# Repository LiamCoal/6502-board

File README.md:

# 6502-board
*Experimental 6502 computer.*

## ...why?
Just because I wanted to make something that was not a microcontroller stuck on a board with some capacitors and resistors...

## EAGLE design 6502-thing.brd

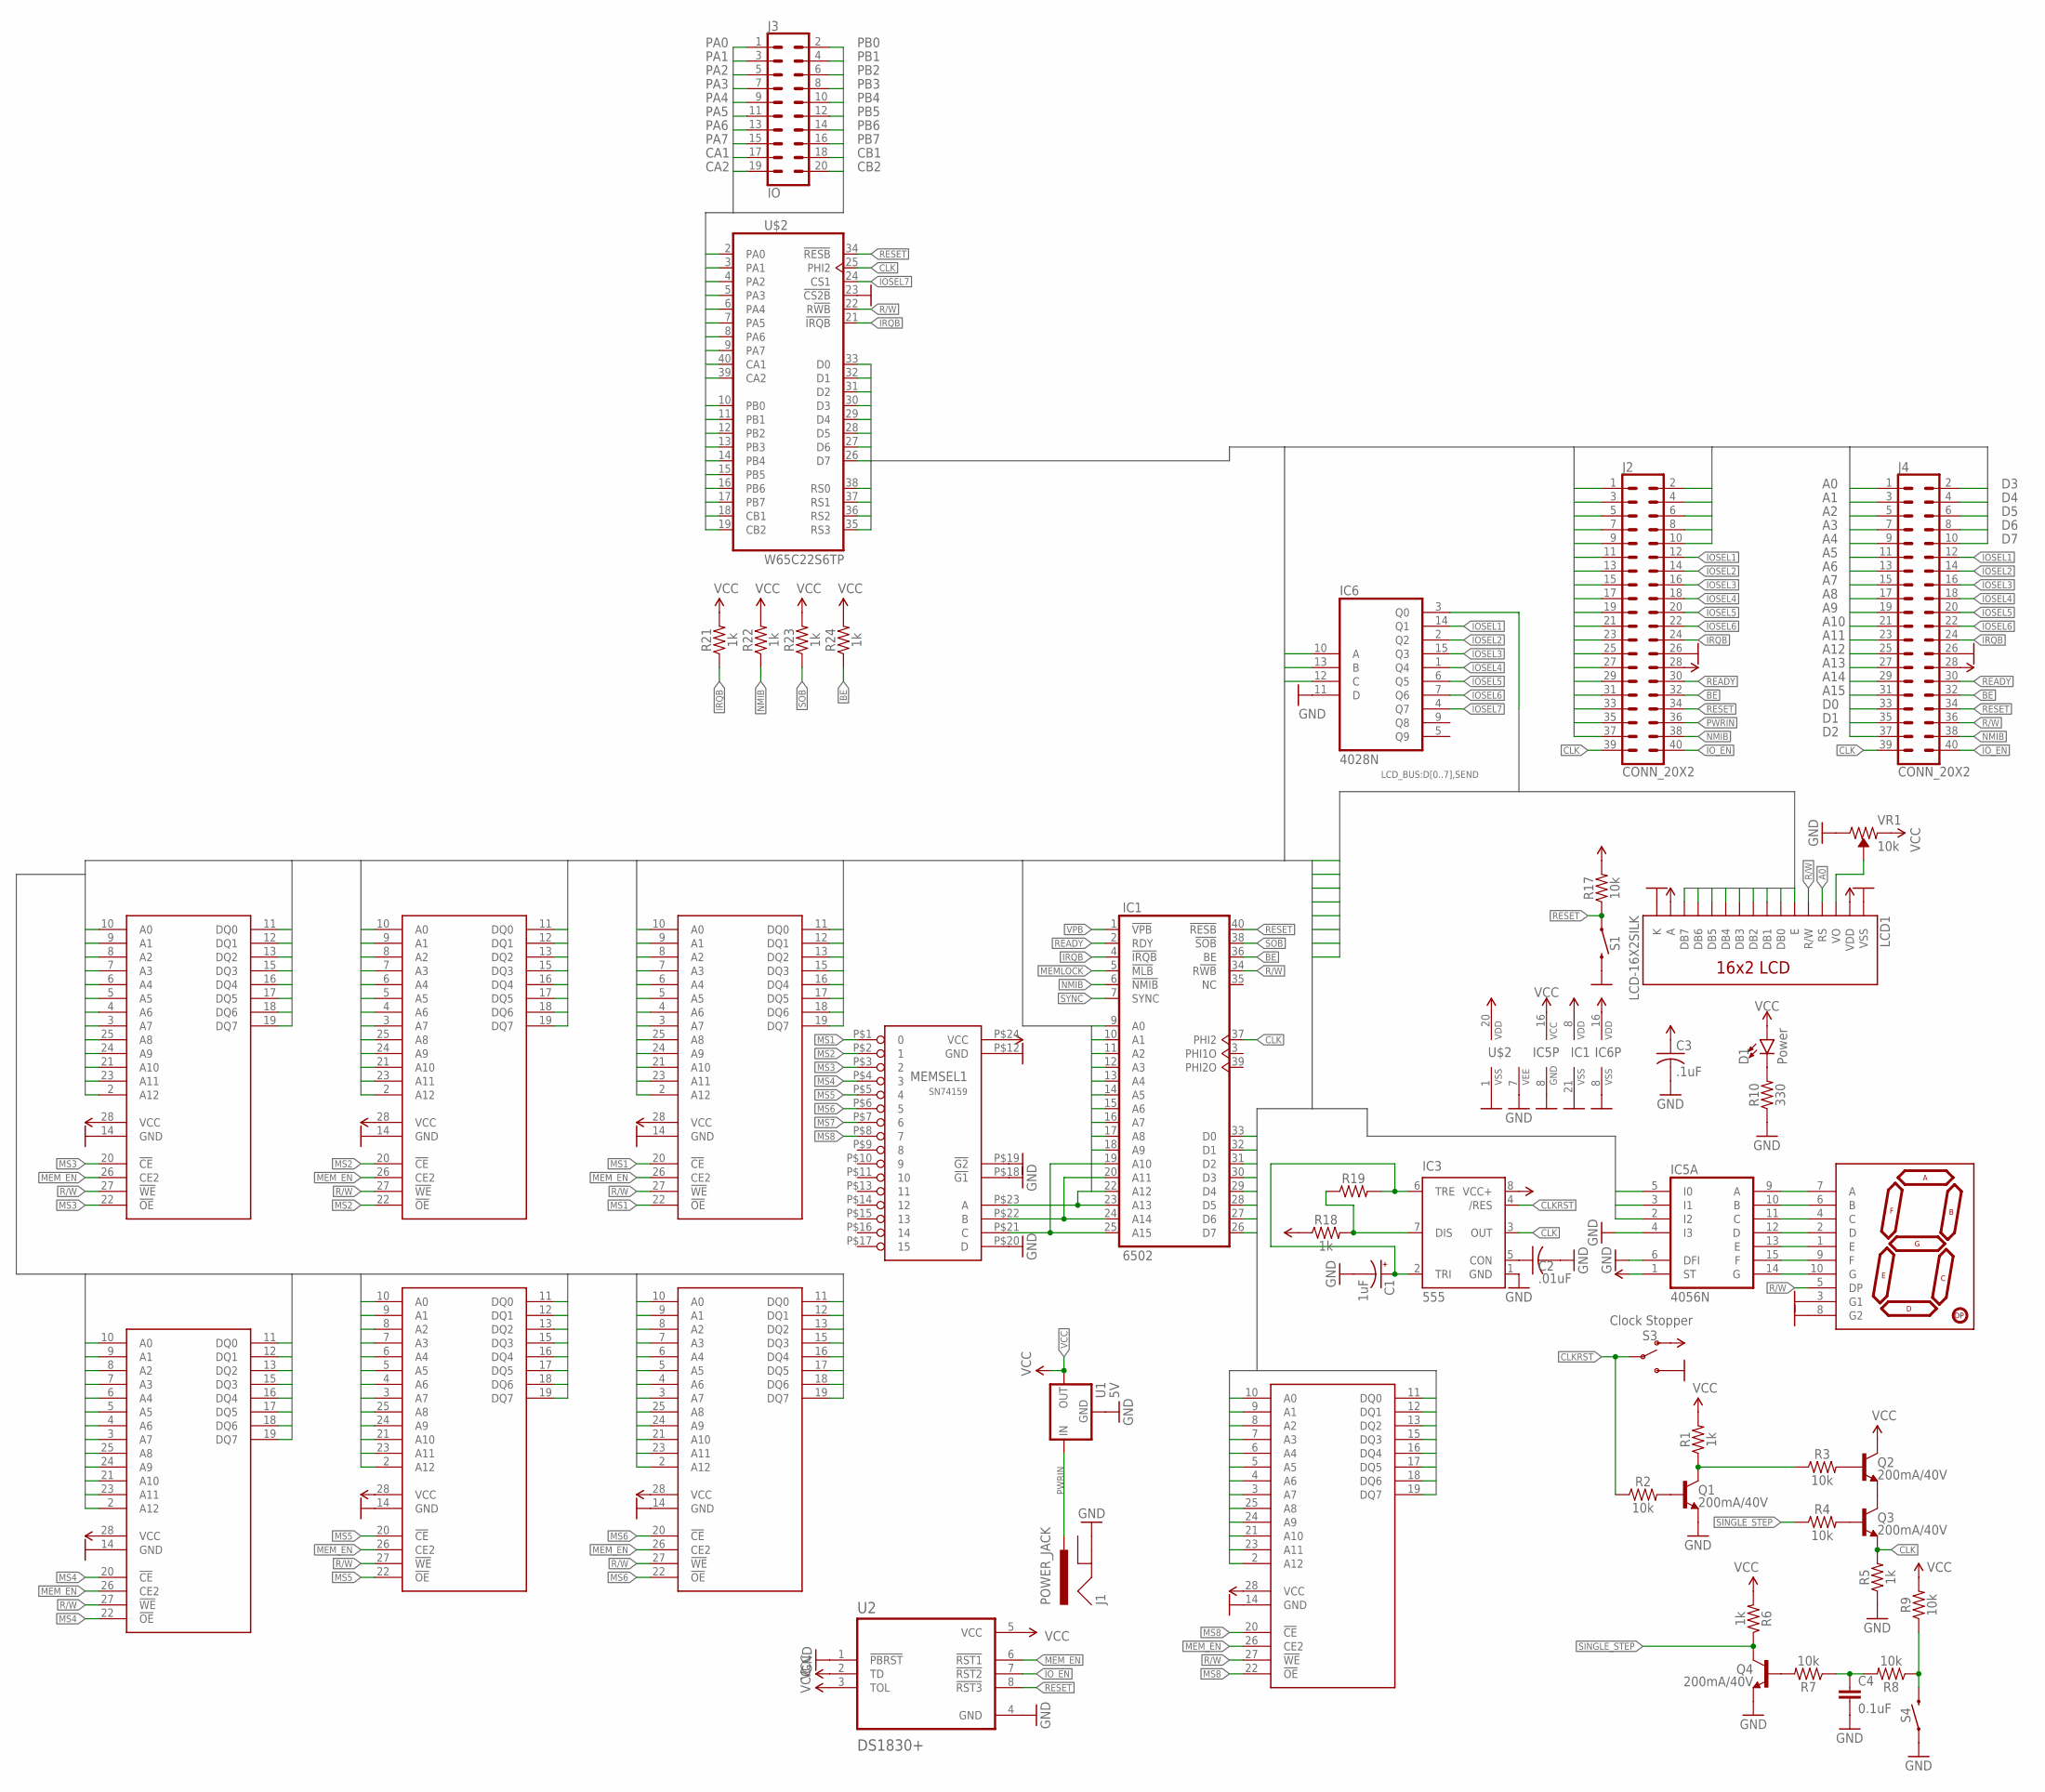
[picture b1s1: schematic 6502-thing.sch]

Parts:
C1: 1uF; E3,5-8
C2: .01uF; C025-024X044
C3: .1uF; C025-024X044
C4: 0.1uF; CAP-PTH-SMALL-KIT
D1: Power; LED_5MM
EEPROM1: AS6C6264DIP28; 0.6"_DIP28
IC1: 6502; DIL40
IC3: 555; DIP08
IC5: 4056N; DIL16
IC6: 4028N; DIL16
J1: POWER_JACK; POWER_JACK_PTH
J2, J4: CONN_20X2; 2X20
J3: IO; 2X10
LCD1: LCD-16X2SILK; LCD-16X2
MEMORY1, MEMORY2, MEMORY3, MEMORY4, MEMORY5, MEMORY6: AS6C6264DIP28; 0.6"_DIP28
MEMSEL1: SN74159; 0.6"_DIP24
Q1, Q2, Q3, Q4: 200mA/40V; TO-92
R1, R5, R6, R18, R19, R21, R22, R23, R24: 1k; AXIAL-0.3
R2, R3, R4, R7, R8, R9, R17: 10k; AXIAL-0.3
R10: 330; AXIAL-0.3
S1, S4: MOMENTARY-SWITCH-SPST-PTH-6.0MM; TACTILE_SWITCH_PTH_6.0MM
S3: Clock Stopper; SWITCH_SPDT_PTH_11.6X4.0MM
U1: 5V; TO-220-ALT
U2: DS1830+; DIP794W47P254L991H457Q8
U$1: YSD-160AB3C-8; 7-SEGMENT-1"PTH
U$2: W65C22S6TP; DIL40
VR1: 10k; TRIMPOT-PTH-3386U

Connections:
A0: EEPROM1.10 (A0), IC1.9 (A0), J2.1, J4.1, LCD1.4 (RS), MEMORY1.10 (A0), MEMORY2.10 (A0), MEMORY3.10 (A0), MEMORY4.10 (A0), MEMORY5.10 (A0), MEMORY6.10 (A0), U$2.38 (RS0)
A1: EEPROM1.9 (A1), IC1.10 (A1), J2.3, J4.3, MEMORY1.9 (A1), MEMORY2.9 (A1), MEMORY3.9 (A1), MEMORY4.9 (A1), MEMORY5.9 (A1), MEMORY6.9 (A1), U$2.37 (RS1)
A2: EEPROM1.8 (A2), IC1.11 (A2), J2.5, J4.5, MEMORY1.8 (A2), MEMORY2.8 (A2), MEMORY3.8 (A2), MEMORY4.8 (A2), MEMORY5.8 (A2), MEMORY6.8 (A2), U$2.36 (RS2)
A3: EEPROM1.7 (A3), IC1.12 (A3), J2.7, J4.7, MEMORY1.7 (A3), MEMORY2.7 (A3), MEMORY3.7 (A3), MEMORY4.7 (A3), MEMORY5.7 (A3), MEMORY6.7 (A3), U$2.35 (RS3)
A4: EEPROM1.6 (A4), IC1.13 (A4), J2.9, J4.9, MEMORY1.6 (A4), MEMORY2.6 (A4), MEMORY3.6 (A4), MEMORY4.6 (A4), MEMORY5.6 (A4), MEMORY6.6 (A4)
A5: EEPROM1.5 (A5), IC1.14 (A5), J2.11, J4.11, MEMORY1.5 (A5), MEMORY2.5 (A5), MEMORY3.5 (A5), MEMORY4.5 (A5), MEMORY5.5 (A5), MEMORY6.5 (A5)
A6: EEPROM1.4 (A6), IC1.15 (A6), J2.13, J4.13, MEMORY1.4 (A6), MEMORY2.4 (A6), MEMORY3.4 (A6), MEMORY4.4 (A6), MEMORY5.4 (A6), MEMORY6.4 (A6)
A7: EEPROM1.3 (A7), IC1.16 (A7), J2.15, J4.15, MEMORY1.3 (A7), MEMORY2.3 (A7), MEMORY3.3 (A7), MEMORY4.3 (A7), MEMORY5.3 (A7), MEMORY6.3 (A7)
A8: EEPROM1.25 (A8), IC1.17 (A8), J2.17, J4.17, MEMORY1.25 (A8), MEMORY2.25 (A8), MEMORY3.25 (A8), MEMORY4.25 (A8), MEMORY5.25 (A8), MEMORY6.25 (A8)
A9: EEPROM1.24 (A9), IC1.18 (A9), J2.19, J4.19, MEMORY1.24 (A9), MEMORY2.24 (A9), MEMORY3.24 (A9), MEMORY4.24 (A9), MEMORY5.24 (A9), MEMORY6.24 (A9)
A10: EEPROM1.21 (A10), IC1.19 (A10), IC6.10 (A), J2.21, J4.21, MEMORY1.21 (A10), MEMORY2.21 (A10), MEMORY3.21 (A10), MEMORY4.21 (A10), MEMORY5.21 (A10), MEMORY6.21 (A10)
A11: EEPROM1.23 (A11), IC1.20 (A11), IC6.13 (B), J2.23, J4.23, MEMORY1.23 (A11), MEMORY2.23 (A11), MEMORY3.23 (A11), MEMORY4.23 (A11), MEMORY5.23 (A11), MEMORY6.23 (A11)
A12: EEPROM1.2 (A12), IC1.22 (A12), IC6.12 (C), J2.25, J4.25, MEMORY1.2 (A12), MEMORY2.2 (A12), MEMORY3.2 (A12), MEMORY4.2 (A12), MEMORY5.2 (A12), MEMORY6.2 (A12)
A13: IC1.23 (A13), IC5.5 (I0), J2.27, J4.27, MEMSEL1.P$23 (A)
A14: IC1.24 (A14), IC5.3 (I1), J2.29, J4.29, MEMSEL1.P$22 (B)
A15: IC1.25 (A15), IC5.2 (I2), J2.31, J4.31, MEMSEL1.P$21 (C)
BE: IC1.36 (BE), J2.32, J4.32, R24.P$1 (1)
CA1: J3.17, U$2.40 (CA1)
CA2: J3.19, U$2.39 (CA2)
CB1: J3.18, U$2.18 (CB1)
CB2: J3.20, U$2.19 (CB2)
CLK: IC1.37 (PHI2), IC3.3 (OUT), J2.39, J4.39, Q3.1 (E), R5.P$2 (2), U$2.25 (PHI2)
CLKRST: IC3.4 (/RES), R2.P$1 (1), S3.2
D0: EEPROM1.11 (DQ0), IC1.33 (D0), J2.33, J4.33, LCD1.7 (DB0), MEMORY1.11 (DQ0), MEMORY2.11 (DQ0), MEMORY3.11 (DQ0), MEMORY4.11 (DQ0), MEMORY5.11 (DQ0), MEMORY6.11 (DQ0), U$2.33 (D0)
D1: EEPROM1.12 (DQ1), IC1.32 (D1), J2.35, J4.35, LCD1.8 (DB1), MEMORY1.12 (DQ1), MEMORY2.12 (DQ1), MEMORY3.12 (DQ1), MEMORY4.12 (DQ1), MEMORY5.12 (DQ1), MEMORY6.12 (DQ1), U$2.32 (D1)
D2: EEPROM1.13 (DQ2), IC1.31 (D2), J2.37, J4.37, LCD1.9 (DB2), MEMORY1.13 (DQ2), MEMORY2.13 (DQ2), MEMORY3.13 (DQ2), MEMORY4.13 (DQ2), MEMORY5.13 (DQ2), MEMORY6.13 (DQ2), U$2.31 (D2)
D3: EEPROM1.15 (DQ3), IC1.30 (D3), J2.2, J4.2, LCD1.10 (DB3), MEMORY1.15 (DQ3), MEMORY2.15 (DQ3), MEMORY3.15 (DQ3), MEMORY4.15 (DQ3), MEMORY5.15 (DQ3), MEMORY6.15 (DQ3), U$2.30 (D3)
D4: EEPROM1.16 (DQ4), IC1.29 (D4), J2.4, J4.4, LCD1.11 (DB4), MEMORY1.16 (DQ4), MEMORY2.16 (DQ4), MEMORY3.16 (DQ4), MEMORY4.16 (DQ4), MEMORY5.16 (DQ4), MEMORY6.16 (DQ4), U$2.29 (D4)
D5: EEPROM1.17 (DQ5), IC1.28 (D5), J2.6, J4.6, LCD1.12 (DB5), MEMORY1.17 (DQ5), MEMORY2.17 (DQ5), MEMORY3.17 (DQ5), MEMORY4.17 (DQ5), MEMORY5.17 (DQ5), MEMORY6.17 (DQ5), U$2.28 (D5)
D6: EEPROM1.18 (DQ6), IC1.27 (D6), J2.8, J4.8, LCD1.13 (DB6), MEMORY1.18 (DQ6), MEMORY2.18 (DQ6), MEMORY3.18 (DQ6), MEMORY4.18 (DQ6), MEMORY5.18 (DQ6), MEMORY6.18 (DQ6), U$2.27 (D6)
D7: EEPROM1.19 (DQ7), IC1.26 (D7), J2.10, J4.10, LCD1.14 (DB7), MEMORY1.19 (DQ7), MEMORY2.19 (DQ7), MEMORY3.19 (DQ7), MEMORY4.19 (DQ7), MEMORY5.19 (DQ7), MEMORY6.19 (DQ7), U$2.26 (D7)
GND: C1.-, C2.2, C3.2, C4.2, EEPROM1.14 (GND), IC1.21 (VSS), IC3.1 (GND), IC5.4 (I3), IC5.6 (DFI), IC5.7 (VEE), IC5.8 (GND), IC6.8 (VSS), IC6.11 (D), J1.GND, J2.26, J4.26, LCD1.1 (VSS), LCD1.16 (K), MEMORY1.14 (GND), MEMORY2.14 (GND), MEMORY3.14 (GND), MEMORY4.14 (GND), MEMORY5.14 (GND), MEMORY6.14 (GND), MEMSEL1.P$12 (GND), MEMSEL1.P$18 (!G1!), MEMSEL1.P$19 (!G2!), MEMSEL1.P$20 (D), Q1.1 (E), Q4.1 (E), R5.P$1 (1), R10.P$1 (1), S1.3 (2), S3.3 (S), S4.1, U1.GND, U2.1 (!PBRST), U2.4 (GND), U$1.3 (G1), U$1.8 (G2), U$2.1 (VSS), U$2.23 (!CS2B), VR1.3 (CW)
IOSEL1: IC6.14 (Q1), J2.12, J4.12
IOSEL2: IC6.2 (Q2), J2.14, J4.14
IOSEL3: IC6.15 (Q3), J2.16, J4.16
IOSEL4: IC6.1 (Q4), J2.18, J4.18
IOSEL5: IC6.6 (Q5), J2.20, J4.20
IOSEL6: IC6.7 (Q6), J2.22, J4.22
IOSEL7: IC6.4 (Q7), U$2.24 (CS1)
IO_EN: J2.40, J4.40, U2.7 (!RST2)
IRQB: IC1.4 (!IRQB), J2.24, J4.24, R21.P$1 (1), U$2.21 (!IRQB)
MEMLOCK: IC1.5 (!MLB)
MEM_EN: EEPROM1.26 (CE2), MEMORY1.26 (CE2), MEMORY2.26 (CE2), MEMORY3.26 (CE2), MEMORY4.26 (CE2), MEMORY5.26 (CE2), MEMORY6.26 (CE2), U2.6 (!RST1)
MS1: MEMORY1.20 (!CE!), MEMORY1.22 (!OE!), MEMSEL1.P$1 (0)
MS2: MEMORY2.20 (!CE!), MEMORY2.22 (!OE!), MEMSEL1.P$2 (1)
MS3: MEMORY3.20 (!CE!), MEMORY3.22 (!OE!), MEMSEL1.P$3 (2)
MS4: MEMORY4.20 (!CE!), MEMORY4.22 (!OE!), MEMSEL1.P$4 (3)
MS5: MEMORY5.20 (!CE!), MEMORY5.22 (!OE!), MEMSEL1.P$5 (4)
MS6: MEMORY6.20 (!CE!), MEMORY6.22 (!OE!), MEMSEL1.P$6 (5)
MS7: MEMSEL1.P$7 (6)
MS8: EEPROM1.20 (!CE!), EEPROM1.22 (!OE!), MEMSEL1.P$8 (7)
unnamed: Q1.3 (C), R1.P$1 (1), R3.P$1 (1)
unnamed: Q1.2 (B), R2.P$2 (2)
unnamed: Q2.2 (B), R3.P$2 (2)
unnamed: Q3.2 (B), R4.P$2 (2)
unnamed: Q2.1 (E), Q3.3 (C)
unnamed: C1.+, IC3.2 (TRI), IC3.6 (TRE), R19.P$2 (2)
unnamed: Q4.2 (B), R7.P$2 (2)
unnamed: C4.1, R7.P$1 (1), R8.P$2 (2)
unnamed: R8.P$1 (1), R9.P$1 (1), S4.3 (2)
unnamed: D1.K (C), R10.P$2 (2)
unnamed: LCD1.3 (VO), VR1.2 (WIPER)
unnamed: IC3.7 (DIS), R18.P$2 (2), R19.P$1 (1)
unnamed: C2.1, IC3.5 (CON)
unnamed: IC5.9 (A), U$1.7 (A)
unnamed: IC5.10 (B), U$1.6 (B)
unnamed: IC5.11 (C), U$1.4 (C)
unnamed: IC5.12 (D), U$1.2 (D)
unnamed: IC5.13 (E), U$1.1 (E)
unnamed: IC5.15 (F), U$1.9 (F)
unnamed: IC5.14 (G), U$1.10 (G)
NMIB: IC1.6 (!NMIB), J2.38, J4.38, R22.P$1 (1)
PA0: J3.1, U$2.2 (PA0)
PA1: J3.3, U$2.3 (PA1)
PA2: J3.5, U$2.4 (PA2)
PA3: J3.7, U$2.5 (PA3)
PA4: J3.9, U$2.6 (PA4)
PA5: J3.11, U$2.7 (PA5)
PA6: J3.13, U$2.8 (PA6)
PA7: J3.15, U$2.9 (PA7)
PB0: J3.2, U$2.10 (PB0)
PB1: J3.4, U$2.11 (PB1)
PB2: J3.6, U$2.12 (PB2)
PB3: J3.8, U$2.13 (PB3)
PB4: J3.10, U$2.14 (PB4)
PB5: J3.12, U$2.15 (PB5)
PB6: J3.14, U$2.16 (PB6)
PB7: J3.16, U$2.17 (PB7)
PWRIN: J1.PWR, J2.36, U1.IN
R/W: EEPROM1.27 (!WE!), IC1.34 (R!WB), J4.36, LCD1.5 (R/W), MEMORY1.27 (!WE!), MEMORY2.27 (!WE!), MEMORY3.27 (!WE!), MEMORY4.27 (!WE!), MEMORY5.27 (!WE!), MEMORY6.27 (!WE!), U$1.5 (DP), U$2.22 (R!WB)
READY: IC1.2 (RDY), J2.30, J4.30
RESET: IC1.40 (!RESB), J2.34, J4.34, R17.P$1 (1), S1.1, U2.8 (!RST3), U$2.34 (!RESB)
SEND: IC6.3 (Q0), LCD1.6 (E)
SINGLE_STEP: Q4.3 (C), R4.P$1 (1), R6.P$1 (1)
SOB: IC1.38 (!SOB), R23.P$1 (1)
SYNC: IC1.7 (SYNC)
VCC: C3.1, D1.A, EEPROM1.28 (VCC), IC1.8 (VDD), IC3.8 (VCC+), IC5.1 (ST), IC5.16 (VCC), IC6.16 (VDD), J2.28, J4.28, LCD1.2 (VDD), LCD1.15 (A), MEMORY1.28 (VCC), MEMORY2.28 (VCC), MEMORY3.28 (VCC), MEMORY4.28 (VCC), MEMORY5.28 (VCC), MEMORY6.28 (VCC), MEMSEL1.P$24 (VCC), Q2.3 (C), R1.P$2 (2), R6.P$2 (2), R9.P$2 (2), R17.P$2 (2), R18.P$1 (1), R21.P$2 (2), R22.P$2 (2), R23.P$2 (2), R24.P$2 (2), S3.1 (O), U1.OUT, U2.2 (TD), U2.3 (TOL), U2.5 (VCC), U$2.20 (VDD), VR1.1 (CCW)
VPB: IC1.1 (!VPB)

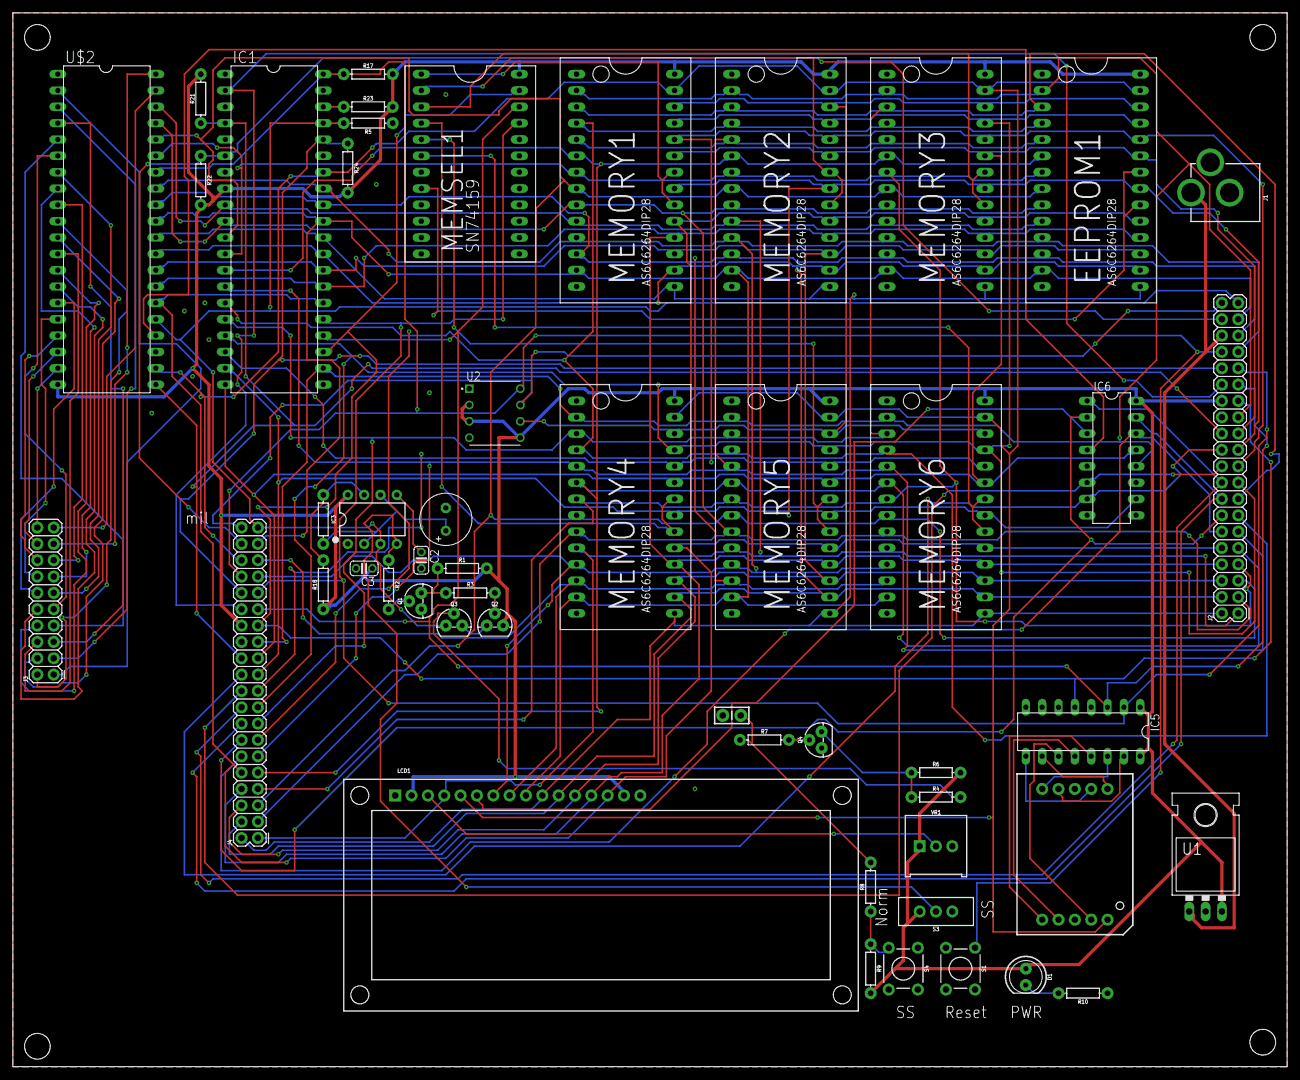
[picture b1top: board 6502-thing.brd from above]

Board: 2 copper layers, 198.1 x 163.8 mm, 51 parts (0 on the bottom side), 94 nets.

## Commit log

2020-02-29 Add 6502 board.
2020-03-01 (liam forgot what he did in this commit)
2020-03-07 Clean up code.
2020-03-07 Move around Silkscreen a little bit.
2020-03-07 Remove useless pdf folder.
2020-03-07 Move pin definitions to main schematic file
2020-03-07 Add library to simplify creating expansions.
2020-03-08 Pins wrong size... fixed!
2020-03-11 Route board.
2020-03-11 Change version of eagle.

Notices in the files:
parts and their libraries:
SparkFun-Resistors: Licensing: Creative Commons ShareAlike 4.0 International - https://creativecommons.org/licenses/by-sa/4.0
